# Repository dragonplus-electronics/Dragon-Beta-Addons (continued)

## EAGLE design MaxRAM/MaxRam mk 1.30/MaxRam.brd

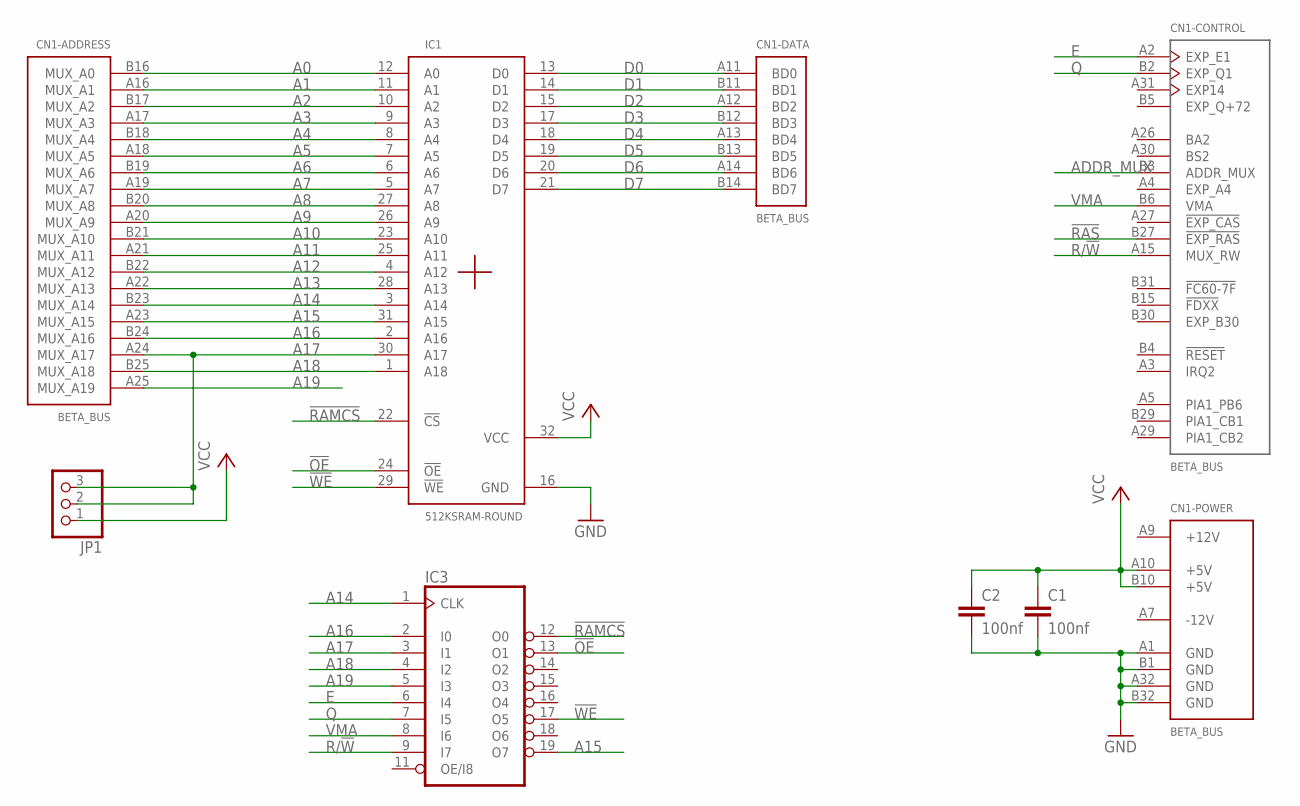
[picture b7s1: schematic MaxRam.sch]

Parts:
C1, C2: 100nf; C025-025X050
CN1: BETA_BUS; MAB64
IC1: 512KSRAM-ROUND; DIL32-ROUND
IC3: 16V8-ROUND; DIL20-R
JP1: PINHD-1X3; 1X03

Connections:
!OE: IC1.24 (!OE), IC3.13 (O1)
!RAMCS: IC1.22 (!CS), IC3.12 (O0)
!RAS: CN1.B27 (!EXP_RAS)
!WE: IC1.29 (!WE), IC3.17 (O5)
+12V: CN1.A9 (+12V)
-12V: CN1.A7 (-12V)
A0: CN1.B16 (MUX_A0), IC1.12 (A0)
A1: CN1.A16 (MUX_A1), IC1.11 (A1)
A2: CN1.B17 (MUX_A2), IC1.10 (A2)
A3: CN1.A17 (MUX_A3), IC1.9 (A3)
A4: CN1.B18 (MUX_A4), IC1.8 (A4)
A5: CN1.A18 (MUX_A5), IC1.7 (A5)
A6: CN1.B19 (MUX_A6), IC1.6 (A6)
A7: CN1.A19 (MUX_A7), IC1.5 (A7)
A8: CN1.B20 (MUX_A8), IC1.27 (A8)
A9: CN1.A20 (MUX_A9), IC1.26 (A9)
A10: CN1.B21 (MUX_A10), IC1.23 (A10)
A11: CN1.A21 (MUX_A11), IC1.25 (A11)
A12: CN1.B22 (MUX_A12), IC1.4 (A12)
A13: CN1.A22 (MUX_A13), IC1.28 (A13)
A14: CN1.B23 (MUX_A14), IC1.3 (A14), IC3.1 (CLK)
A15: CN1.A23 (MUX_A15), IC1.31 (A15), IC3.19 (O7)
A16: CN1.B24 (MUX_A16), IC1.2 (A16), IC3.2 (I0)
A17: CN1.A24 (MUX_A17), IC1.30 (A17), IC3.3 (I1), JP1.2, JP1.3
A18: CN1.B25 (MUX_A18), IC1.1 (A18), IC3.4 (I2)
A19: CN1.A25 (MUX_A19), IC3.5 (I3)
ADDR_MUX: CN1.B3 (ADDR_MUX)
D0: CN1.A11 (BD0), IC1.13 (D0)
D1: CN1.B11 (BD1), IC1.14 (D1)
D2: CN1.A12 (BD2), IC1.15 (D2)
D3: CN1.B12 (BD3), IC1.17 (D3)
D4: CN1.A13 (BD4), IC1.18 (D4)
D5: CN1.B13 (BD5), IC1.19 (D5)
D6: CN1.A14 (BD6), IC1.20 (D6)
D7: CN1.B14 (BD7), IC1.21 (D7)
E: CN1.A2 (EXP_E1), IC3.6 (I4)
GND: C1.2, C2.2, CN1.A1 (GND), CN1.A32 (GND), CN1.B1 (GND), CN1.B32 (GND), IC1.16 (GND), IC3.10 (GND)
Q: CN1.B2 (EXP_Q1), IC3.7 (I5)
R/!W: CN1.A15 (MUX_RW), IC3.9 (I7)
VCC: C1.1, C2.1, CN1.A10 (+5V), CN1.B10 (+5V), IC1.32 (VCC), IC3.20 (VCC), JP1.1
VMA: CN1.B6 (VMA), IC3.8 (I6)

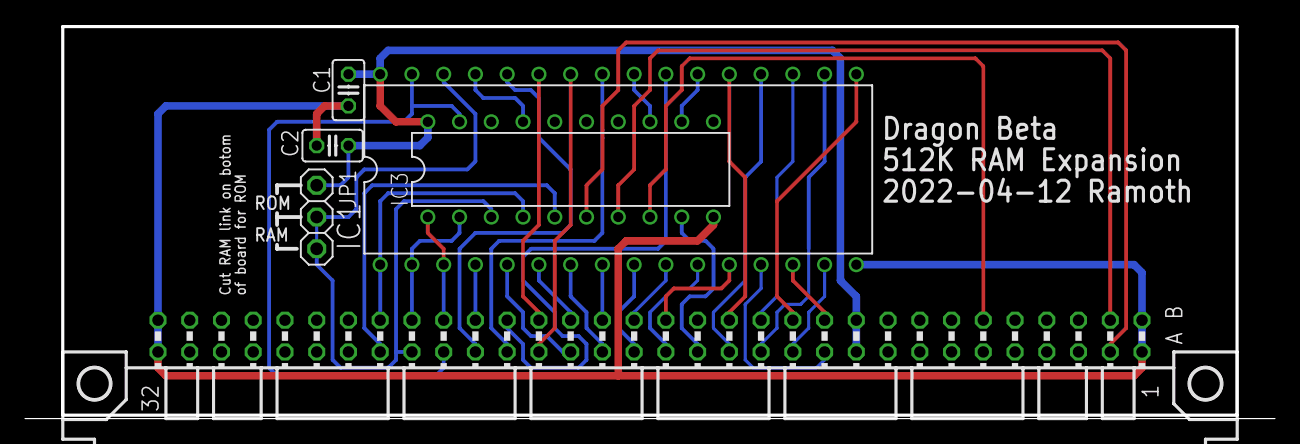
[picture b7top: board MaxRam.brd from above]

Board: 2 copper layers, 99.8 x 31.2 mm, 6 parts (0 on the bottom side), 37 nets.

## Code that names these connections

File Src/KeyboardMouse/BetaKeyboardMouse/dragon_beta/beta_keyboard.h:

/*
    Dragon Beta Keyboard emulation implementation.

    2022-08-25, Phill Harvey-Smith.
*/
#include "hardware/gpio.h"

#ifndef __BETA_KBD__
#define __BETA_KBD__

#define MATRIX_ROWS 10
#define ROW_MASK    0x03FF

//I/O Pins

#define OCDI        10
#define INPUT_LOAD  11
#define DATA_OUT    12
#define ANY_KEY     13

#define INPUT_LOAD_MASK     (1 << INPUT_LOAD)
#define OCDI_MASK           (1 << OCDI)

typedef struct  {
    bool    ParalellSerial;         // If true then parallel load, else serial shift on clock.
    uint8_t Buffer;
    uint8_t Shifter;                // shift data
} shifter_t;



// Initialize, setup input keys & interrupts.
void Beta_KeyInit(void);

// Act on a keypress from the real keyboard, Key pressed if UpDown is true, released if false.
void Beta_KeyUD(uint8_t Key,
                bool    UpDown);

// Deal with modifier keys, shifts, ctrl, alt etc
void Beta_KeyModifiers(uint8_t  Shifts);

// Callback called at the end of processing of a keyboard report
void KeyDoneCallback(void);

// Called from main loop, must not block!
void Beta_KeyTask(void);

void NewKeybaordIRQ(void);

void NewKeybaordInLdIRQ(void);
void NewKeybaordOCDIIRQ(void);

void KeyboardIRQ(uint       PinNo, 
                 uint32_t   Events);

#endif

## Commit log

2024-09-30 Initial commit.
    Initial commit of code and schematics.
